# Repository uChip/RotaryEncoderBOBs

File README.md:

# Rotary Encoder Breakout PCBs  

Eagle CAD PCB designs for rotary encoder breakout boards. 
Converts the following rotary encoders to 0.1" breadboard format.  
  * TT Electronics: EN12-VS  
  * Bourns: PEC16-2xxxF-Sxxxx  

See one of the following links for drivers that interpret the gray-code on an Arduino.  
  * https://github.com/uChip/Rotary  
  * https://github.com/BrianLow/Rotary  
  * http://www.buxtronix.net/2011/10/rotary-encoders-done-properly.html  

The PCBs come in different layouts.  The "edge" layout brings all connections to a single row of 0.1" spaced pins.  The "straddle" layout brings signals to two rows of 0.1" spaced pins.  The rows are 0.4" apart such that they will straddle the center channel of common solderless breadboards.

## Component Description  

The encoders listed are "gray-code" encoders.  They also have a push-button switch (normally open).
 
Digi-Key part numbers  
  * EN12-VS: several part #s, search "EN12", example #987-1198-ND  
  * PEC16: several part #s, search "PEC16" example #PEC16-2215F-S0024-ND   

Pinout on PCB or see datasheets.  

## Order PCBs  

You will be able to order any of these PCBs from OSH Park.  Click on one of the following links.
  * EN12-VS edge - http://www.oshpark.com/shared_projects/ICXpkCPn  
  * PEC16 edge - http://www.oshpark.com/shared_projects/QfFKi2uG

## Status
  * EN12-VS edge - PCB layout tested to be correct, holes have been enlarged in latest rev to ease assembly  
  * PEC16 edge - PCB layout tested to be correct.  
  * PEC16 straddle - not yet tested, board not yet ordered   

## File Formats  

Design files are in "CadSoft EAGLE PCB Design Software" .brd and .sch formats.  
A free version of the software can be downloaded from www.cadsoftusa.com.  

## Distribution License  

All PCB designs in this repo are Public Domain.  No liability accepted.

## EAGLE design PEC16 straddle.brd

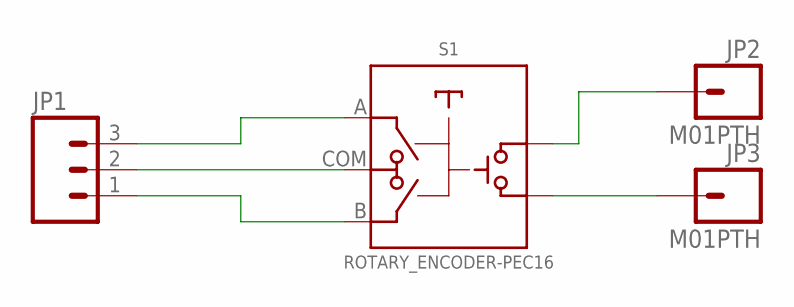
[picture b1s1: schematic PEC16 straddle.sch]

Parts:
JP1: M03PTH; 1X03
JP2, JP3: M01PTH; 1X01
S1: ROTARY_ENCODER-PEC16; PEC16-2XXX

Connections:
unnamed: JP3.1, S1.P$5
unnamed: JP1.3, S1.A
unnamed: JP1.2, S1.COM
unnamed: JP1.1, S1.B
unnamed: JP2.1, S1.P$4

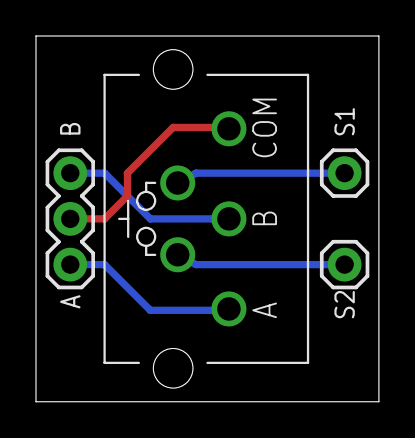
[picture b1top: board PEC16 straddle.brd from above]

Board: 2 copper layers, 19.1 x 20.3 mm, 4 parts (0 on the bottom side), 5 nets.

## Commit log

2013-10-14 Elaborated on README
2013-10-14 More elaboration and formatting edits to README
2013-10-21 Ordered PEC16 edge. Updated README.
    PEC16 as ordered from OSH Park 20OCT2013.
    Added PEC16 links & status to README.
    Added OSH Park rendering of PEC16 edge PCB.
2013-10-24 increased hole size. Updated README.
    Increased pin hole size from 0.039 to 0.043 to ease assembly.
2013-11-03 Updated README w current status
2014-02-07 Edit README to announce PEC16 edge tested

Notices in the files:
parts and their libraries:
SparkFun-Connectors: Licensing: CC v3.0 Share-Alike You are welcome to use this library for commercial purposes.
